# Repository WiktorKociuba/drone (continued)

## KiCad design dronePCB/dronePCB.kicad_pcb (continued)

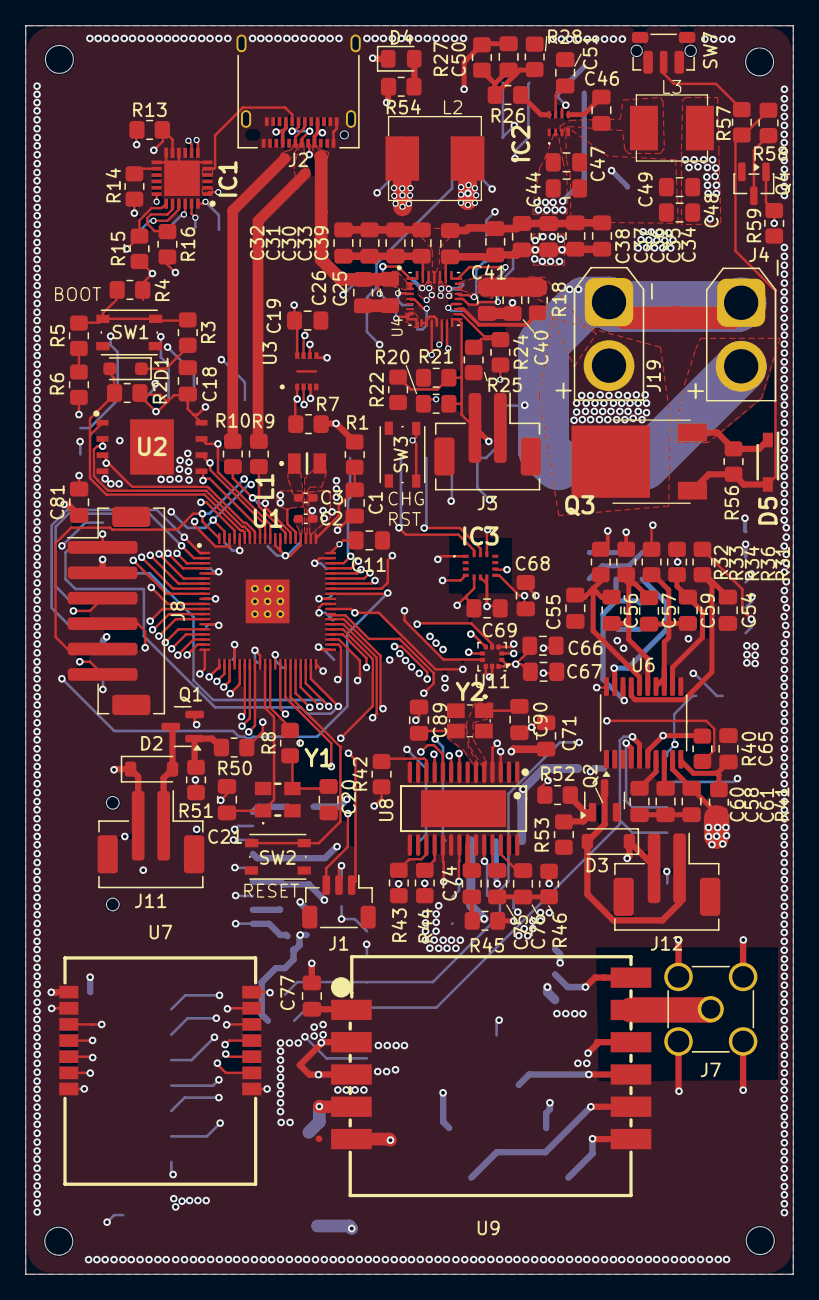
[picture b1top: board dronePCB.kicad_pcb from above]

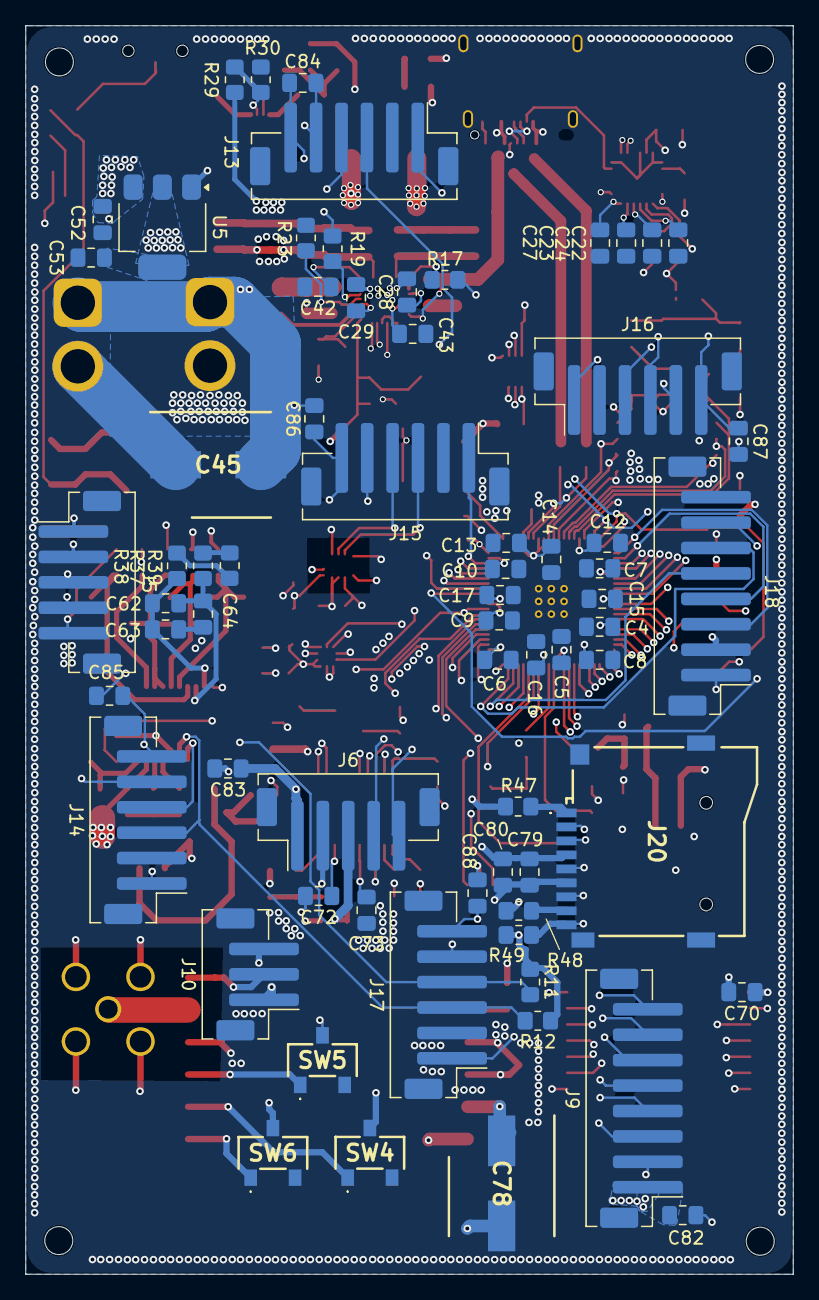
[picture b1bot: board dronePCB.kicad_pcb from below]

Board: 6 copper layers, 60.4 x 98.2 mm, 205 parts (68 on the bottom side), 140 nets.

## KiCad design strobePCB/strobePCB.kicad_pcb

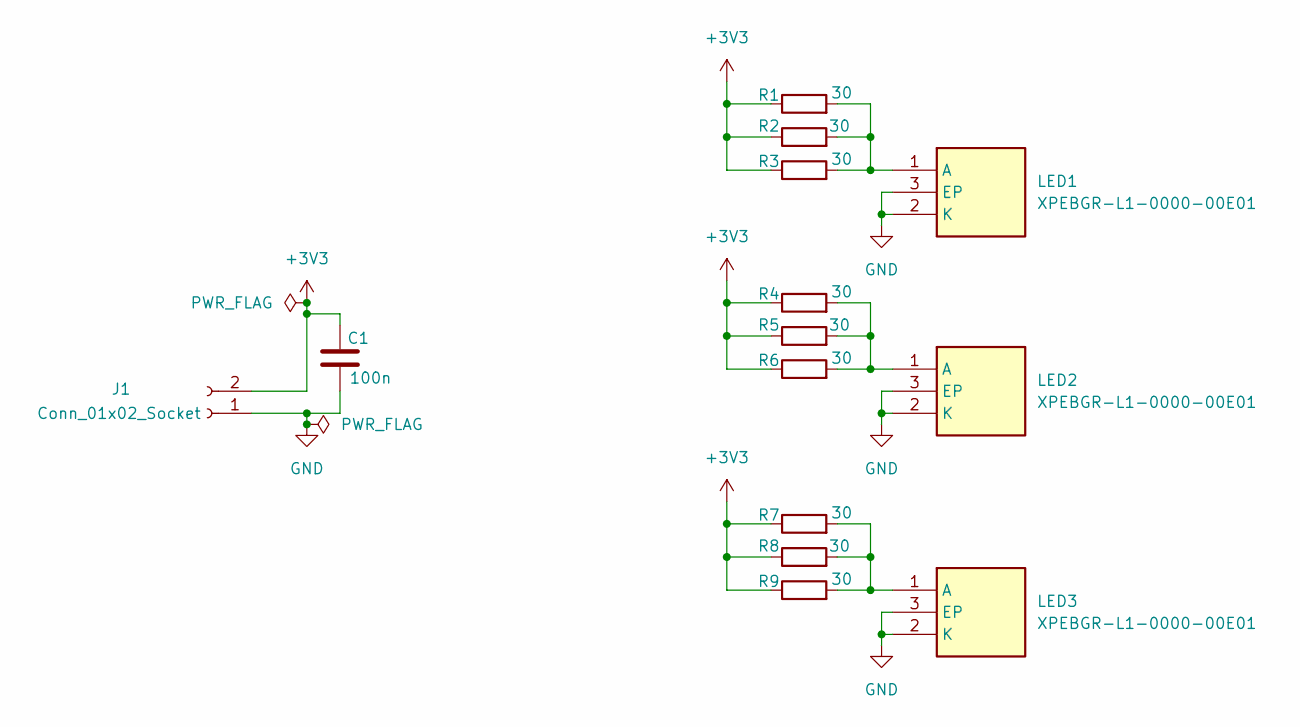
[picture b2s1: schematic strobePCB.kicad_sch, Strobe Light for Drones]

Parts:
C1: 100n; C_0805_2012Metric
J1: Conn_01x02_Socket; JST_PH_B2B-PH-K_1x02_P2.00mm_Vertical
LED1, LED2, LED3: XPEBGR-L1-0000-00E01; XPEBGRL1000000E01; Mouser Part Number 941-XPEBGRL10000E01
R1, R2, R3, R4, R5, R6, R7, R8, R9: 30; R_1210_3225Metric_Pad1.30x2.65mm_HandSolder

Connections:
+3V3: C1.1, J1.2, R1.1, R2.1, R3.1, R4.1, R5.1, R6.1, R7.1, R8.1, R9.1
GND: C1.2, J1.1, LED1.2 (K), LED1.3 (EP), LED2.2 (K), LED2.3 (EP), LED3.2 (K), LED3.3 (EP)
unnamed: LED1.1 (A), R1.2, R2.2, R3.2
unnamed: LED2.1 (A), R4.2, R5.2, R6.2
unnamed: LED3.1 (A), R7.2, R8.2, R9.2

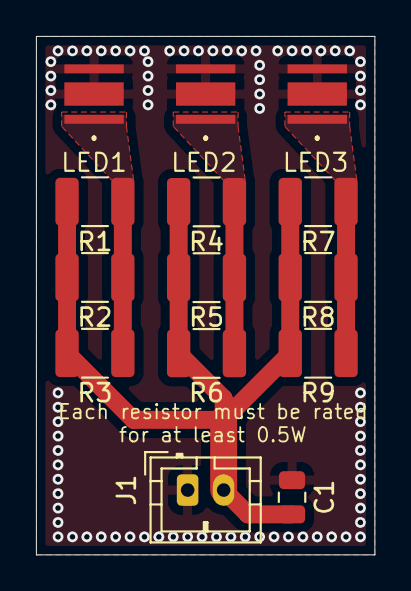
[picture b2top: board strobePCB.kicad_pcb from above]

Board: 2 copper layers, 18.8 x 28.8 mm, 14 parts (0 on the bottom side), 5 nets.

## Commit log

2026-03-27 Added RP2350B and all dependencies, power circuit, IMU, barometer and radio comms.
2026-03-30 Added micro sd card slot
2026-03-31 Added micro SD, GPS, magnetometer, gimbal, DVR, Strobes and ToF sensors
2026-04-01 Added strobe PCB
2026-04-07 Routed RP2350B w/ dependencies + power circuit
2026-04-08 Finished PCB
2026-04-08 Added 3d models to the pcb
2026-04-08 added missing models
2026-04-22 Added power switch
2026-04-23 Started filling the BoM and changed some components
2026-04-24 Added more information to BoM
2026-04-25 Finished the BoM
2026-04-25 commit history
2026-04-25 Embedded 3d models
